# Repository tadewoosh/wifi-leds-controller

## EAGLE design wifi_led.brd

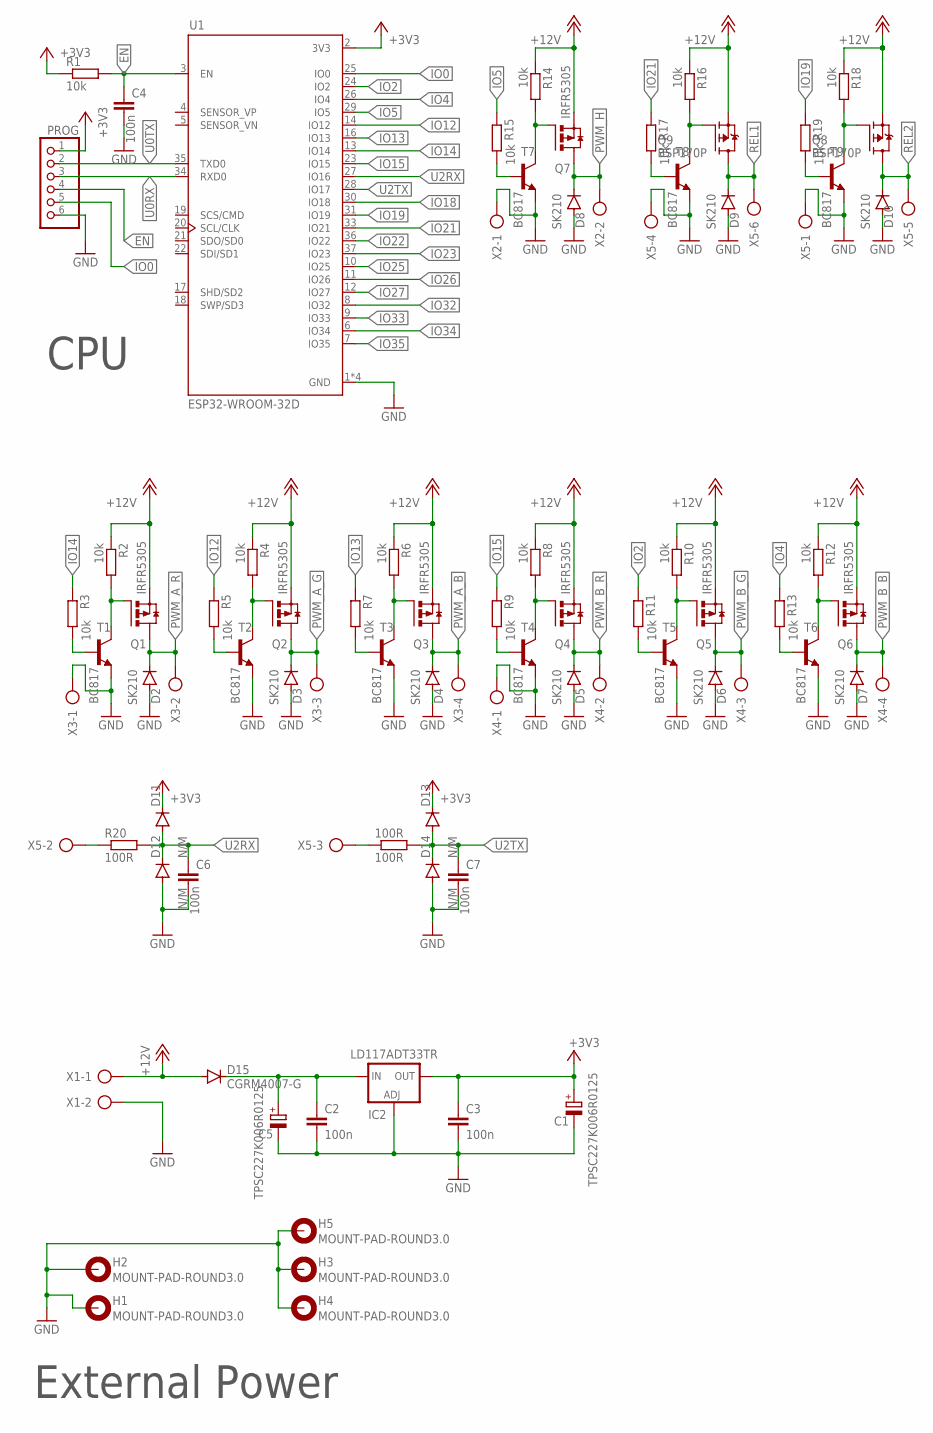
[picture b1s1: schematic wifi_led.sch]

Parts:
100R: 100R; R0603
C1, C5: TPSC227K006R0125; CT6032
C2, C3, C4, C6, C7: 100n; C0603
D2, D3, D4, D5, D6, D7, D8, D9, D10: SK210; SMB
D11, D12, D13, D14: N/M; 0603
D15: CGRM4007-G; SOD-123_MINI-SMA
H1, H2, H3, H4, H5: MOUNT-PAD-ROUND3.0; 3,0-PAD
IC2: LD117ADT33TR; DPACK
PROG: PINHD-1X6; 1X06
Q1, Q2, Q3, Q4, Q5, Q6, Q7: IRFR5305; D-PAK
Q8, Q9: BSP170P; SOT223
R1, R2, R3, R4, R5, R6, R7, R8, R9, R10, R11, R12, R13, R14, R15, R16, R17, R18, R19: 10k; R0603
R20: 100R; R0603
T1, T2, T3, T4, T5, T6, T7, T8, T9: BC817; SOT23-BEC
U1: ESP32-WROOM-32D; MODULE_ESP32-WROOM-32D
X1, X2: AK500/2
X3, X4: AK500/4
X5: AK500/6

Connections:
+3V3: C1.+, C3.1, D11.2 (C), D13.2 (C), IC2.4 (OUT), PROG.1, R1.1, U1.2 (3V3)
+12V: D15.A, Q1.3 (S), Q2.3 (S), Q3.3 (S), Q4.3 (S), Q5.3 (S), Q6.3 (S), Q7.3 (S), Q8.3 (S), Q9.3 (S), R2.1, R4.1, R6.1, R8.1, R10.1, R12.1, R14.1, R16.1, R18.1, X1.1
EN: C4.1, PROG.4, R1.2, U1.3 (EN)
GND: C1.-, C2.2, C3.2, C4.2, C5.-, C6.2, C7.2, D2.A, D3.A, D4.A, D5.A, D6.A, D7.A, D8.A, D9.A, D10.A, D12.1 (A), D14.1 (A), H1.B3,0, H2.B3,0, H3.B3,0, H4.B3,0, H5.B3,0, IC2.1 (ADJ), PROG.6, T1.E, T2.E, T3.E, T4.E, T5.E, T6.E, T7.E, T8.E, T9.E, U1.1 (GND), U1.15 (GND), U1.38 (GND), U1.39 (GND), X1.2, X2.1, X3.1, X4.1, X5.1, X5.4
IO0: PROG.5, U1.25 (IO0)
IO2: R11.1, U1.24 (IO2)
IO4: R13.1, U1.26 (IO4)
IO5: R15.1, U1.29 (IO5)
IO12: R5.1, U1.14 (IO12)
IO13: R7.1, U1.16 (IO13)
IO14: R3.1, U1.13 (IO14)
IO15: R9.1, U1.23 (IO15)
IO18: U1.30 (IO18)
IO19: R19.1, U1.31 (IO19)
IO21: R17.1, U1.33 (IO21)
IO22: U1.36 (IO22)
IO23: U1.37 (IO23)
IO25: U1.10 (IO25)
IO26: U1.11 (IO26)
IO27: U1.12 (IO27)
IO32: U1.8 (IO32)
IO33: U1.9 (IO33)
IO34: U1.6 (IO34)
IO35: U1.7 (IO35)
unnamed: C2.1, C5.+, D15.C, IC2.3 (IN)
unnamed: Q2.1 (G), R4.2, T2.C
unnamed: R5.2, T2.B
unnamed: Q3.1 (G), R6.2, T3.C
unnamed: R7.2, T3.B
unnamed: Q4.1 (G), R8.2, T4.C
unnamed: R9.2, T4.B
unnamed: Q5.1 (G), R10.2, T5.C
unnamed: R11.2, T5.B
unnamed: Q6.1 (G), R12.2, T6.C
unnamed: R13.2, T6.B
unnamed: Q7.1 (G), R14.2, T7.C
unnamed: R15.2, T7.B
unnamed: Q9.1 (G), R16.2, T8.C
unnamed: R17.2, T8.B
unnamed: Q8.1 (G), R18.2, T9.C
unnamed: R19.2, T9.B
unnamed: R20.1, X5.2
unnamed: 100R.1, X5.3
unnamed: Q1.1 (G), R2.2, T1.C
unnamed: R3.2, T1.B
PWM_A_B: D4.C, Q3.4 (D), X3.4
PWM_A_G: D3.C, Q2.4 (D), X3.3
PWM_A_R: D2.C, Q1.4 (D), X3.2
PWM_B_B: D7.C, Q6.4 (D), X4.4
PWM_B_G: D6.C, Q5.4 (D), X4.3
PWM_B_R: D5.C, Q4.4 (D), X4.2
PWM_H: D8.C, Q7.4 (D), X2.2
REL1: D9.C, Q9.2 (D), Q9.4 (D), X5.6
REL2: D10.C, Q8.2 (D), Q8.4 (D), X5.5
U0RX: PROG.3, U1.34 (RXD0)
U0TX: PROG.2, U1.35 (TXD0)
U2RX: C6.1, D11.1 (A), D12.2 (C), R20.2, U1.27 (IO16)
U2TX: 100R.2, C7.1, D13.1 (A), D14.2 (C), U1.28 (IO17)

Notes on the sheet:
External Power
CPU

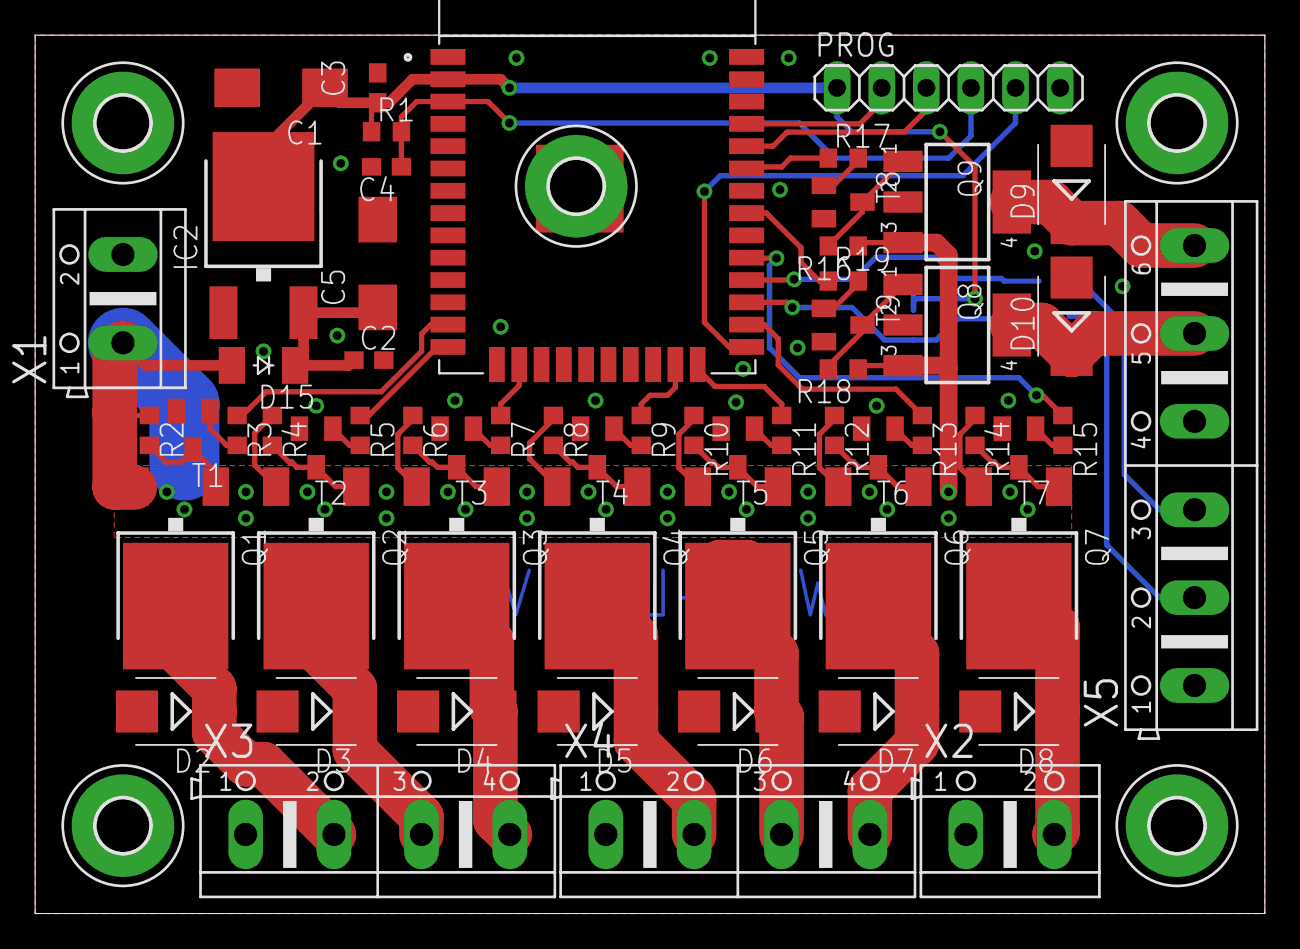
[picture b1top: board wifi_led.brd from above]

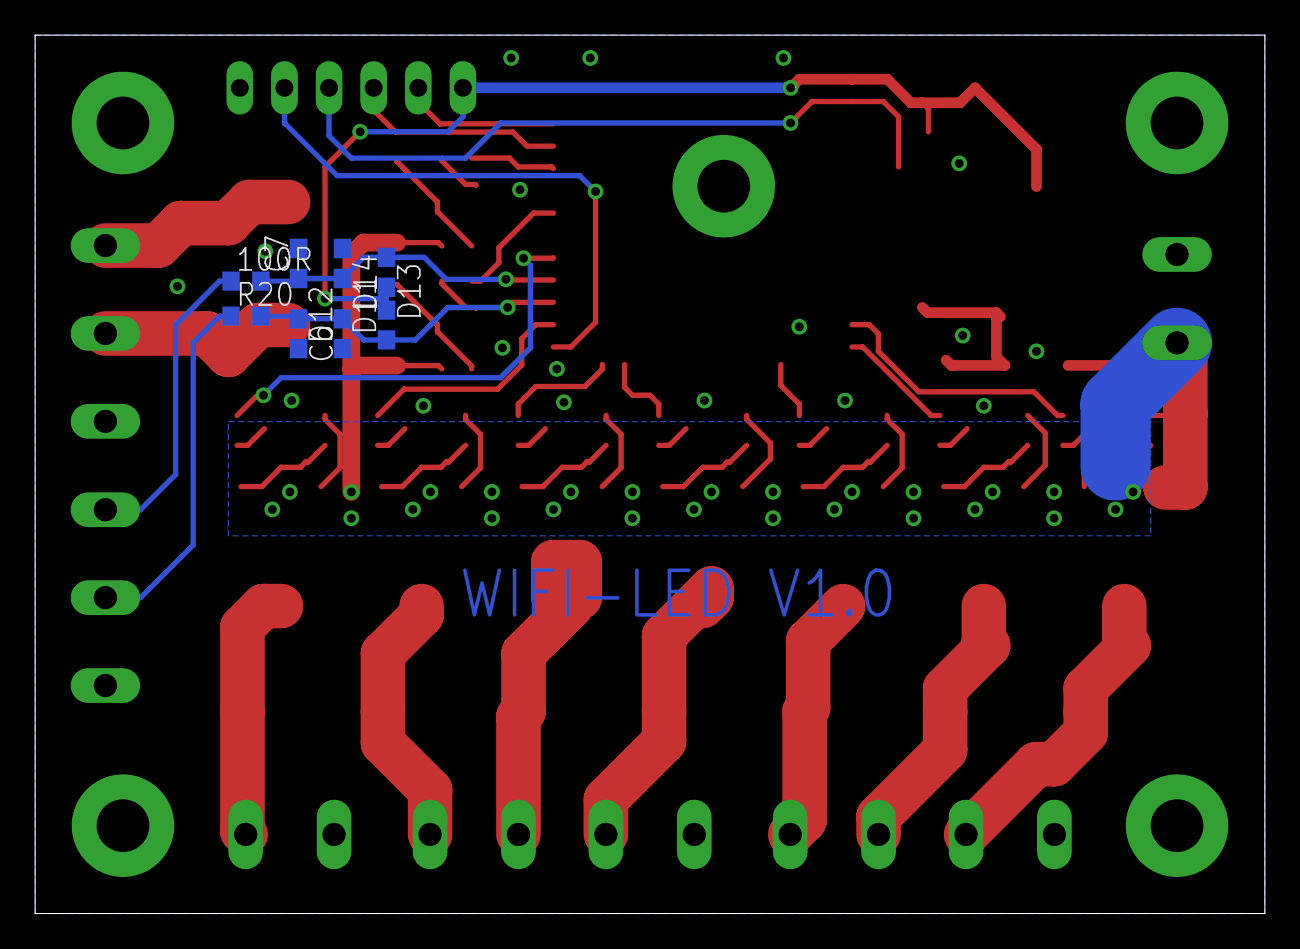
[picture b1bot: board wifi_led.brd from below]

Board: 2 copper layers, 70.0 x 50.0 mm, 73 parts (8 on the bottom side), 48 nets.

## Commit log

2020-10-19 Created project
2020-10-19 Imported from https://tadewoosh@github.com/tadewoosh/wifi-leds-controller.git
